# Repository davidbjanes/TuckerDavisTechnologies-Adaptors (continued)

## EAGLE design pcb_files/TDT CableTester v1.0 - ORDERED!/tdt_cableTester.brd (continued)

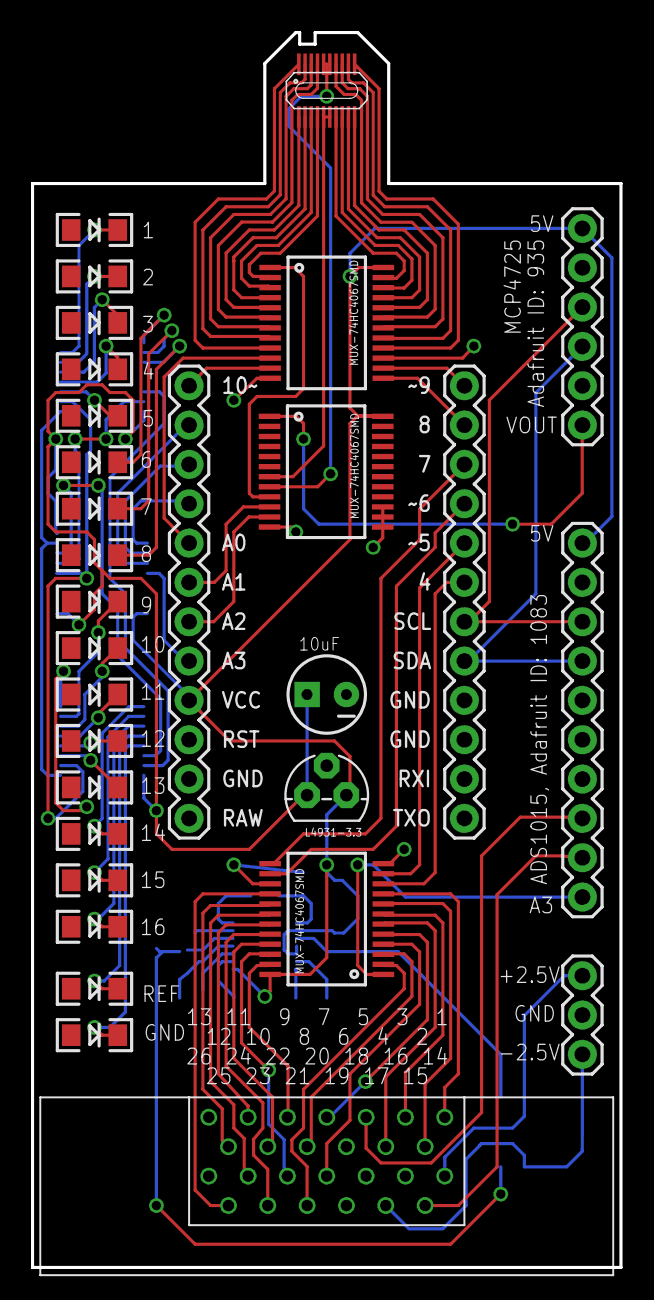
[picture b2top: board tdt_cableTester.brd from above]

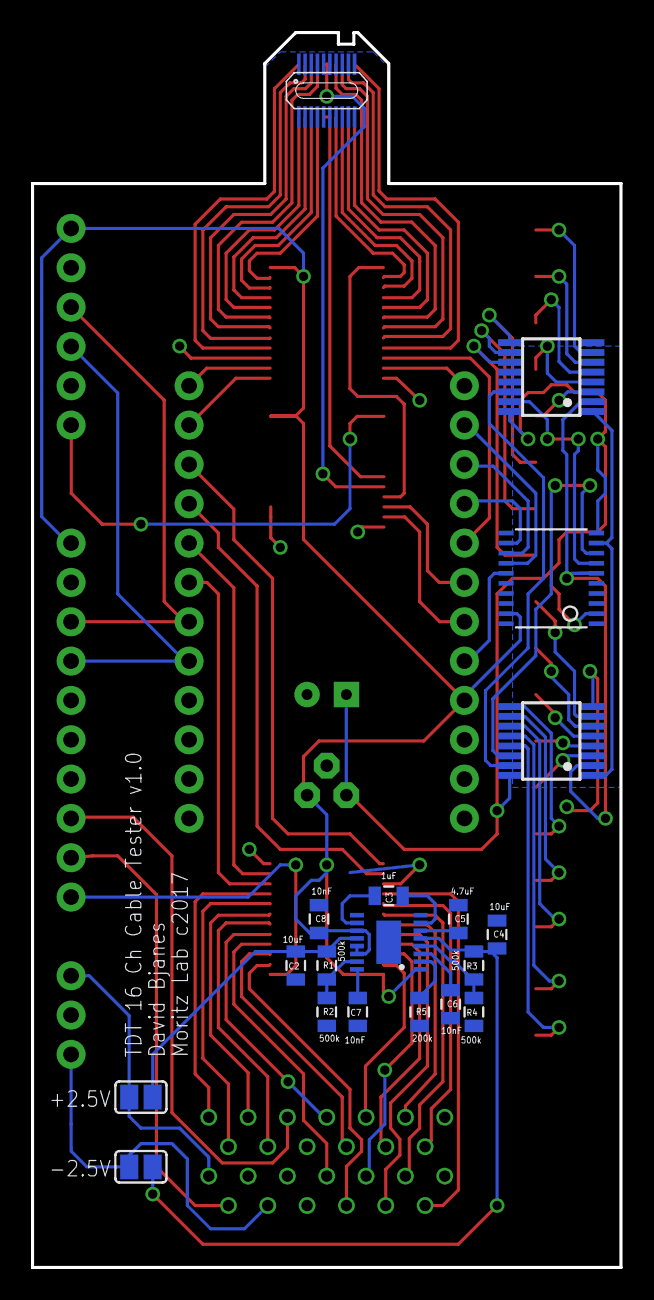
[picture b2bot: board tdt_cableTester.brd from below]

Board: 2 copper layers, 38.0 x 79.8 mm, 49 parts (19 on the bottom side), 94 nets.

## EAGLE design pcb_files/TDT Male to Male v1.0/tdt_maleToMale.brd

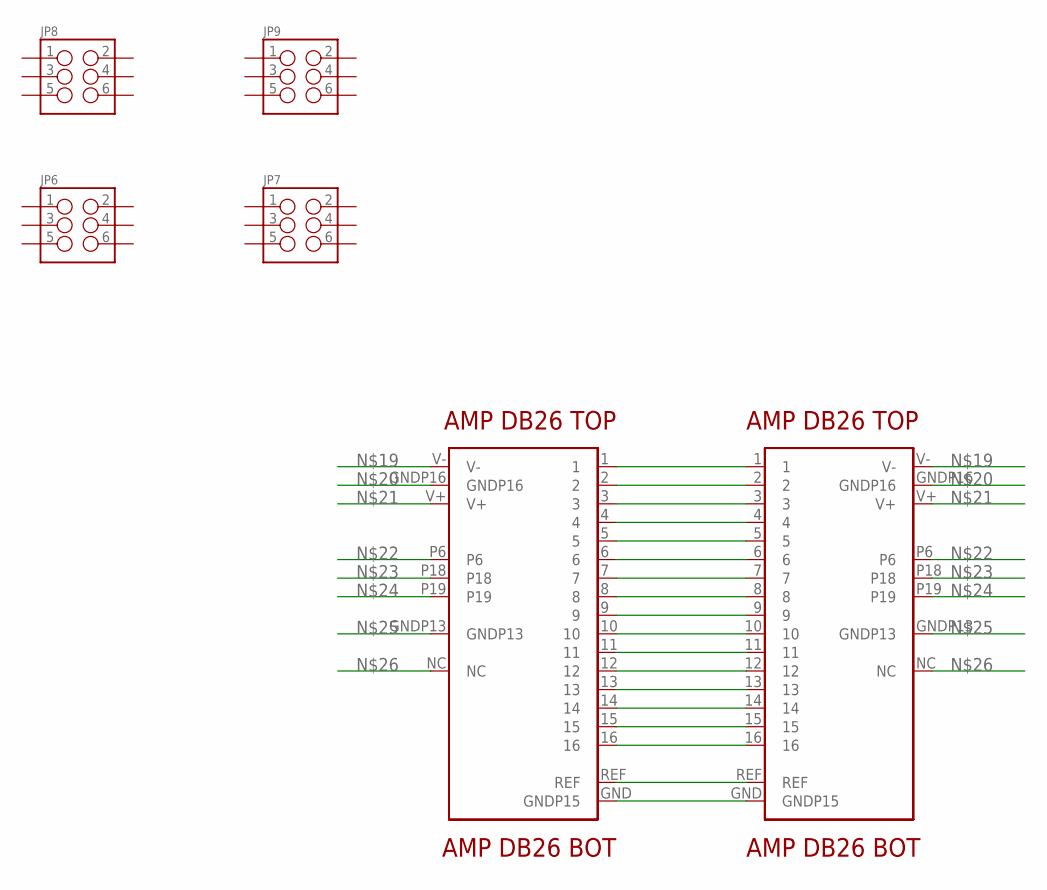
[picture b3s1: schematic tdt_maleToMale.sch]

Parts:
JP6, JP7, JP8, JP9: M03X22X3_SILK_MALE_PTH; 2X3
U$1, U$4: DB26-MALE-BOT
U$2, U$3: DB26-MALE-TOP

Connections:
unnamed: U$2.1, U$3.1
unnamed: U$2.2, U$3.2
unnamed: U$2.3, U$3.3
unnamed: U$2.4, U$3.4
unnamed: U$2.5, U$3.5
unnamed: U$2.REF, U$3.REF
unnamed: U$2.7, U$3.7
unnamed: U$2.9, U$3.9
unnamed: U$2.11, U$3.11
unnamed: U$2.13, U$3.13
unnamed: U$2.15, U$3.15
unnamed: U$1.8, U$4.8
unnamed: U$1.16, U$4.16
unnamed: U$1.GND (GNDP15), U$4.GND (GNDP15)
unnamed: U$1.6, U$4.6
unnamed: U$1.10, U$4.10
unnamed: U$1.12, U$4.12
unnamed: U$1.14, U$4.14
unnamed: U$1.V-, U$4.V-
unnamed: U$1.GNDP16, U$4.GNDP16
unnamed: U$1.V+, U$4.V+
unnamed: U$2.P6, U$3.P6
unnamed: U$1.P18, U$4.P18
unnamed: U$1.P19, U$4.P19
unnamed: U$2.GNDP13, U$3.GNDP13
unnamed: U$1.NC, U$4.NC

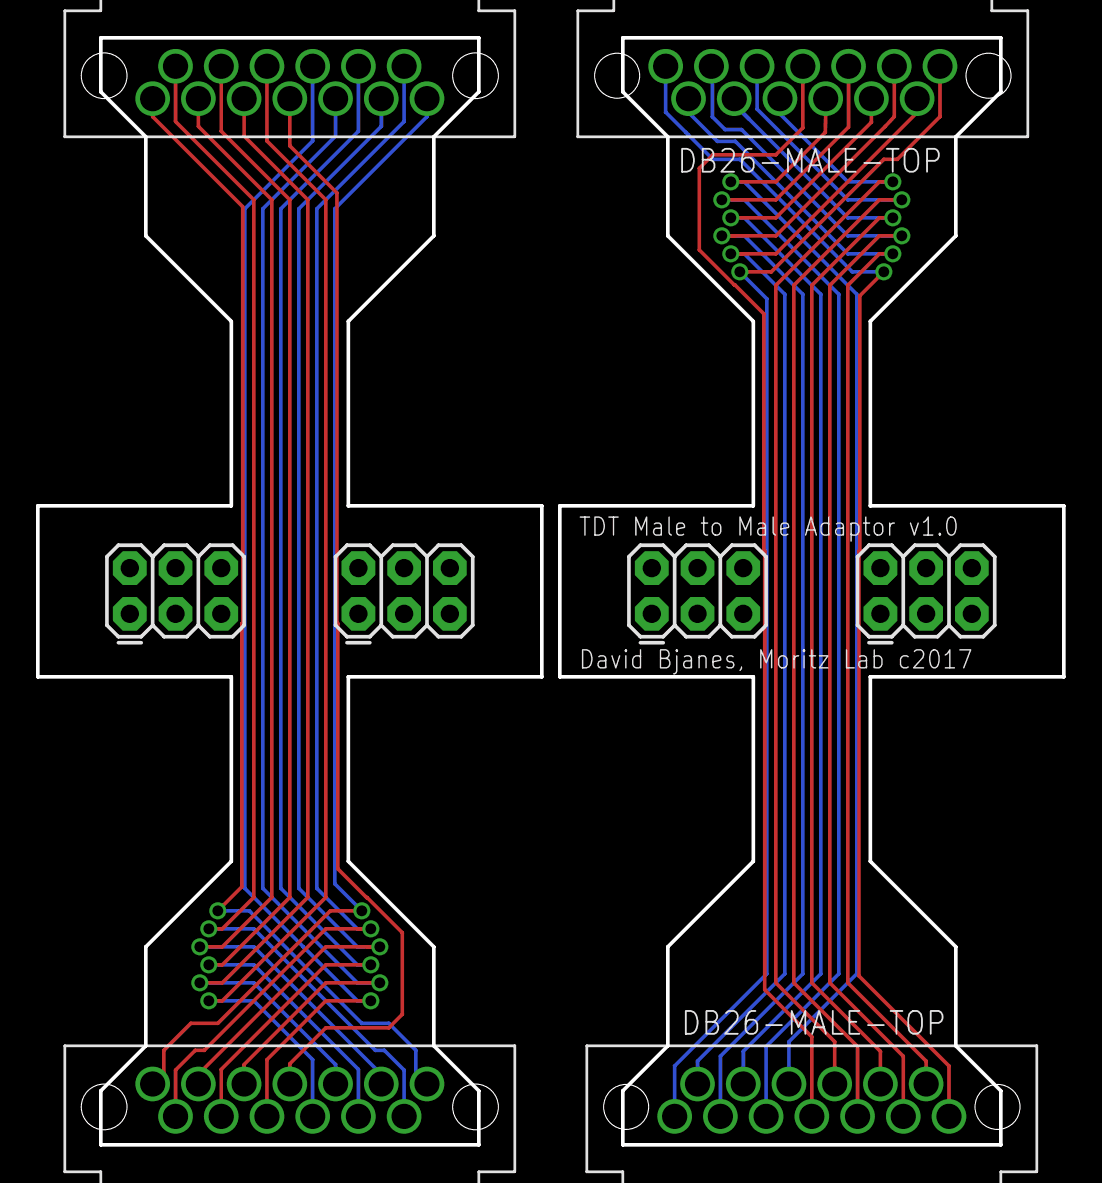
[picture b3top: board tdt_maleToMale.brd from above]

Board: 2 copper layers, 57.0 x 61.5 mm, 8 parts (0 on the bottom side), 26 nets.

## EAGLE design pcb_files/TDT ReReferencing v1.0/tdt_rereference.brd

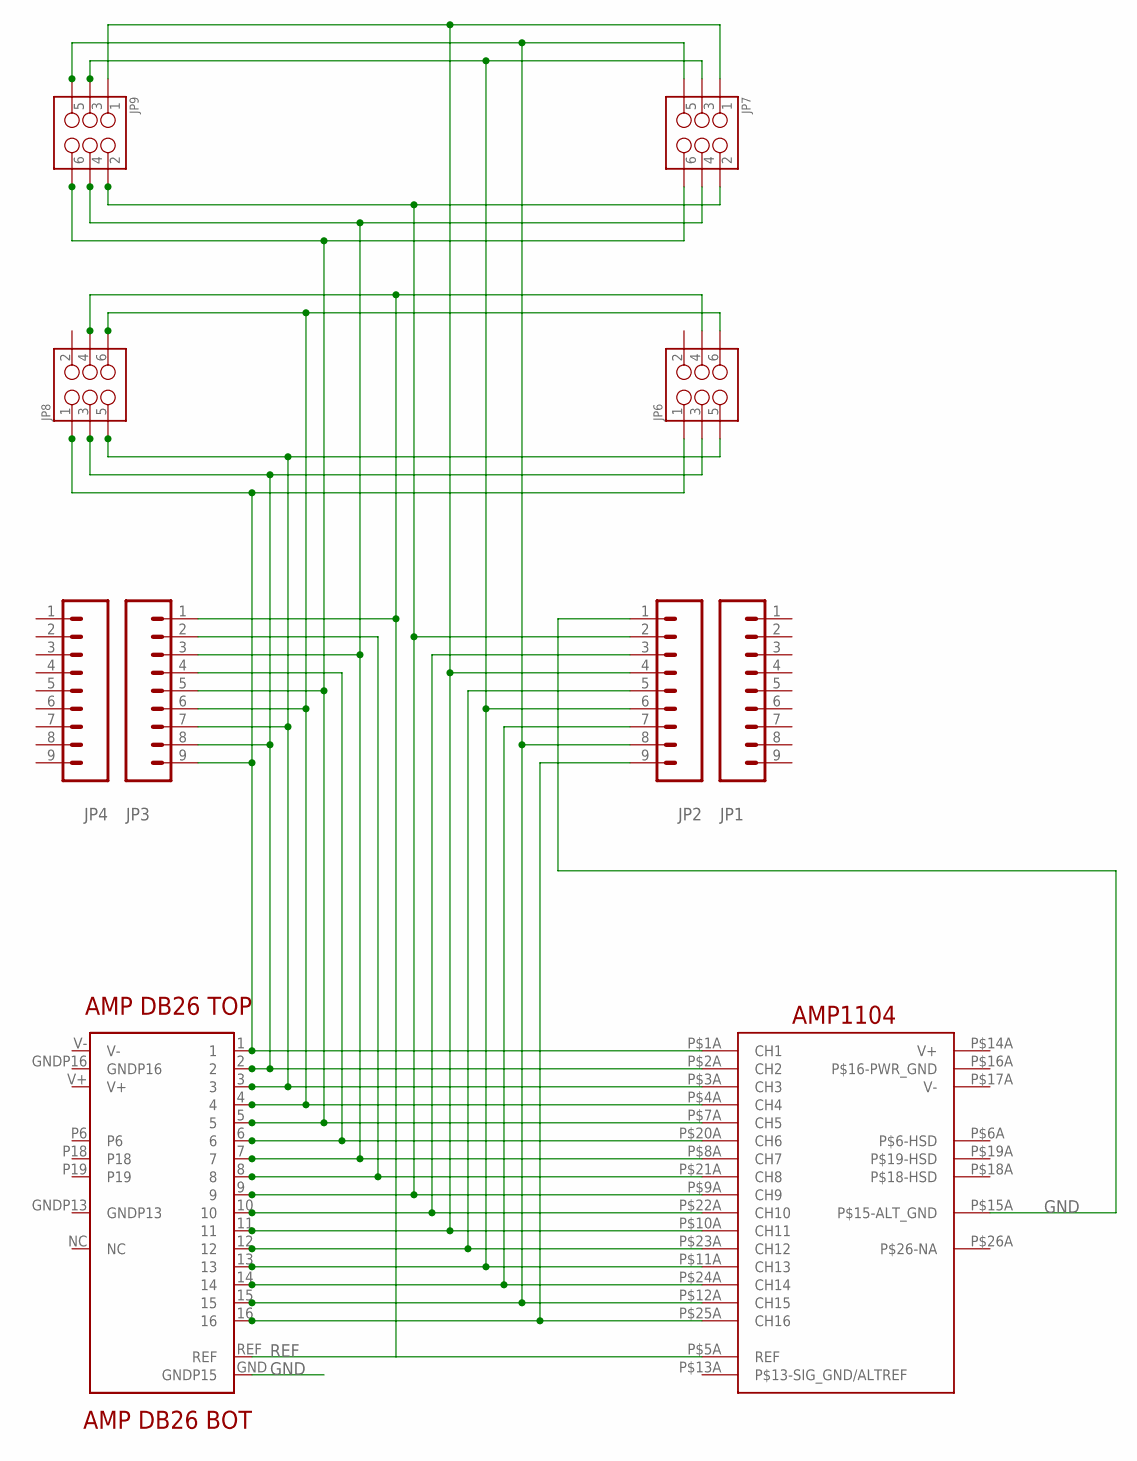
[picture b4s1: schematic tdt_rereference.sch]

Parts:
JP1, JP2, JP3, JP4: M09; 1X09
JP6, JP7, JP8, JP9: M03X22X3_SILK_MALE_PTH; 2X3
U$1: DB26-MALE-BOT
U$2: DB26-MALE-TOP
U$3: AMP1104

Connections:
GND: JP2.1, U$1.GND (GNDP15), U$3.P$15A (P$15-ALT_GND)
unnamed: JP3.9, JP6.1, JP8.1, U$2.1, U$3.P$1A (CH1)
unnamed: JP3.8, JP6.3, JP8.3, U$2.2, U$3.P$2A (CH2)
unnamed: JP3.7, JP6.5, JP8.5, U$2.3, U$3.P$3A (CH3)
unnamed: JP3.6, JP6.6, JP8.6, U$2.4, U$3.P$4A (CH4)
unnamed: JP3.5, JP7.6, JP9.6, U$2.5, U$3.P$7A (CH5)
unnamed: JP3.4, U$1.6, U$3.P$20A (CH6)
unnamed: JP3.3, JP7.4, JP9.4, U$2.7, U$3.P$8A (CH7)
unnamed: JP3.2, U$1.8, U$3.P$21A (CH8)
unnamed: JP2.2, JP7.2, JP9.2, U$2.9, U$3.P$9A (CH9)
unnamed: JP2.4, JP7.1, JP9.1, U$2.11, U$3.P$10A (CH11)
unnamed: JP2.5, U$1.12, U$3.P$23A (CH12)
unnamed: JP2.6, JP7.3, JP9.3, U$2.13, U$3.P$11A (CH13)
unnamed: JP2.7, U$1.14, U$3.P$24A (CH14)
unnamed: JP2.8, JP7.5, JP9.5, U$2.15, U$3.P$12A (CH15)
unnamed: JP2.9, U$1.16, U$3.P$25A (CH16)
unnamed: JP2.3, U$1.10, U$3.P$22A (CH10)
REF: JP3.1, JP6.4, JP8.4, U$2.REF, U$3.P$5A (REF)

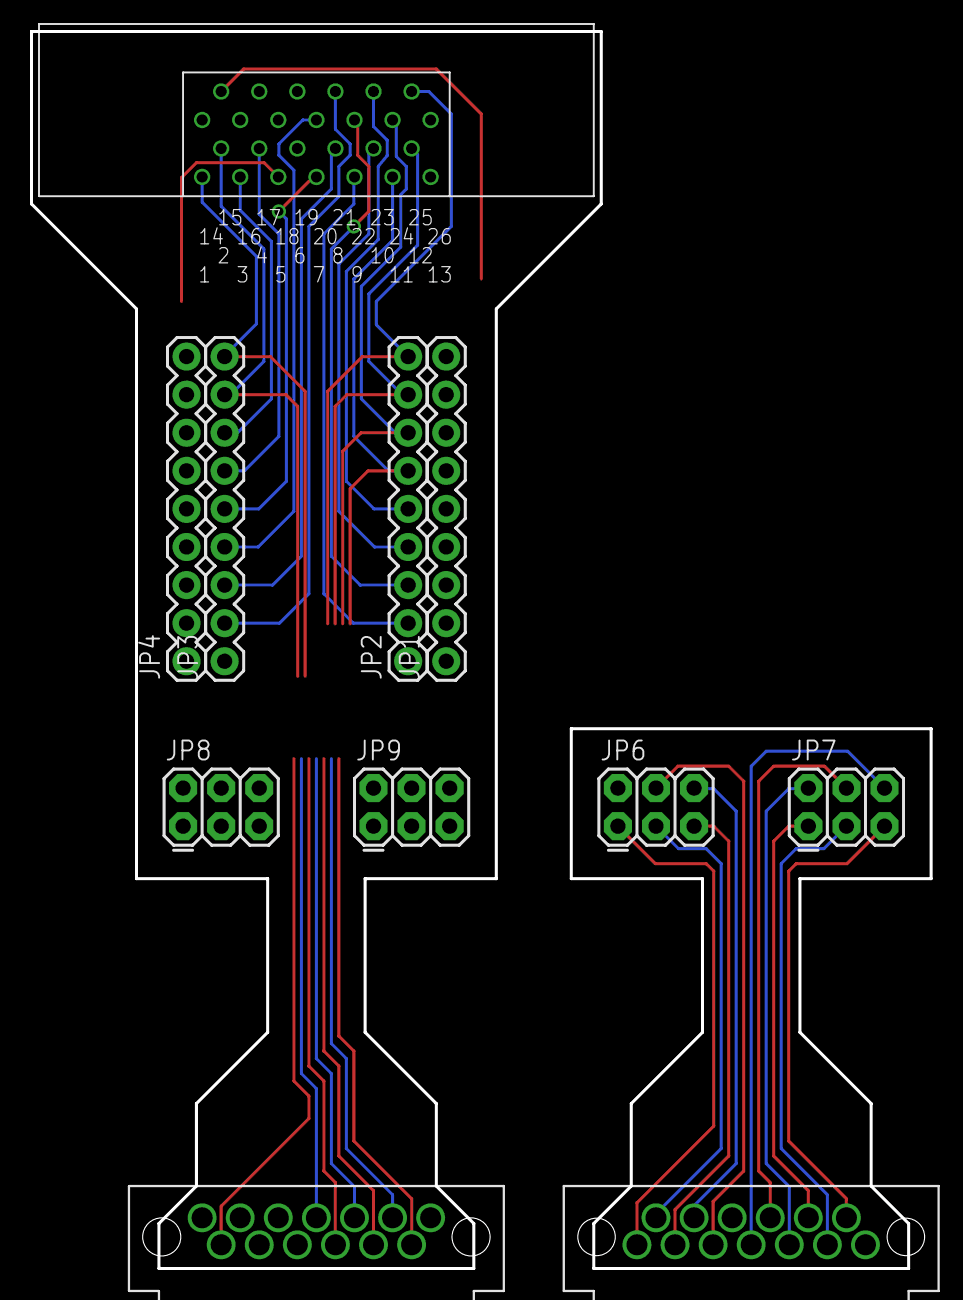
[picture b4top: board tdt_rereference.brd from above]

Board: 2 copper layers, 60.0 x 82.5 mm, 11 parts (0 on the bottom side), 18 nets.
